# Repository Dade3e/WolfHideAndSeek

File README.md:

# WERERABBIT game
## Regole
### Wererabbit
Il gioco è metà tra nascondino e "ce l'hai":
Ogni giocatore ha un arma e i sensori ir,
Minimo di giocatori 3,
Il gioco si divide in wererabbit e rabbits.
Il wererabbit può sparare per passare il suo stato di wererabbit,
i rabbit non possono sparate, solo nascondersi o scappare.

A inizio gioco, il giocatore wererabbit conta per un tempo scelto dal gruppo, gli altri si nascondono.
Ogni giocatore rabbit, ogni circa 10 secondi invia un impulso a 866mhz, il quale è ricevuto dal wererabbit,
che lo visualizza sullo schermo come intensita di segnale trasformata circa in metri e lo aiuterà a cercare i rabbit.

Quando un wererabbit trova e colpisce un rabbit, il colpito diventerà in 60 sec il nuovo wererabbit e il vecchio wererabbit diventerà un rabbit.
Inoltre il vecchio wererabbit è immune al nuovo, ma solo a quello, non ai successivi.

Allo scadere del tempo mostrato a display, perde chi è il wererabbit o lo sta diventando.

### Infected
Ogni giocatore ha un arma e i ricevitori ir.
Il gioco si divide in infetto e sani.

Il gioco inizia con l'infetto che si nasconde.
L'infetto ha il sensore di prossimità il quale vede la distanza dai sani.
Se un sano entra nel raggio dei 5 metri da un infetto, l'infetto può premere il grilletto per infettare il sano.
Se un sano gli spara prima, l'infetto muore.

Il gioco finisce con lo scadere del tempo.
Vincono i più numerosi tra sani e infetti.

### Deathmatch
Classico deathmatch a scquadre o tutti contro tutti,
Se si imposta l'id team a 99, non ci sono squadre e sarà tutti contro tutti.
Una volta colpiti anche solo una volta si muore.
Il gioco finisce allo scadere del tempo.
TODO: vincita?
TODO: tornare alla base per riprendere vita?

### Materiali utilizzati:
- Presa Jack verticale 4 poli: https://www.amazon.it/dp/B089222S84?psc=1&ref=ppx_yo2ov_dt_b_product_details
- EDISION 05-00-0017 Cavo Jack a IR: https://www.amazon.it/dp/B08612KY32?psc=1&ref=ppx_yo2ov_dt_b_product_details
- Esp LoRa32: https://www.amazon.it/dp/B07RWYJQPT?psc=1&ref=ppx_yo2ov_dt_b_product_details
- Led IR SFH 4544: https://it.rs-online.com/web/p/led-a-infrarossi/8108247?sra=pstk
- Transistor 2N2222
- Resistenza da 510/470 Ohm
- Resistenza da 33/27 Ohm
- Pulsante 7 mm: https://www.amazon.it/Gebildet-Precablato-Momentaneo-Temporanei-Ferroviario/dp/B083K1YCZK/ref=sr_1_7?keywords=pulsante&qid=1673539022&sr=8-7&th=1
- Finecorsa da usare come grilletto, forse: https://www.amazon.it/InduSKY-Interruttore-Finecorsa-interruttore-Momentaneo/dp/B08736V215/ref=sr_1_21?keywords=finecorsa&qid=1673539142&sprefix=finecorsa%2Caps%2C115&sr=8-21 
- Morsettiera a vite 2.54: https://www.amazon.it/dp/B08VRD69B6?psc=1&smid=A1LEBA88GLK1VX&ref_=chk_typ_imgToDp

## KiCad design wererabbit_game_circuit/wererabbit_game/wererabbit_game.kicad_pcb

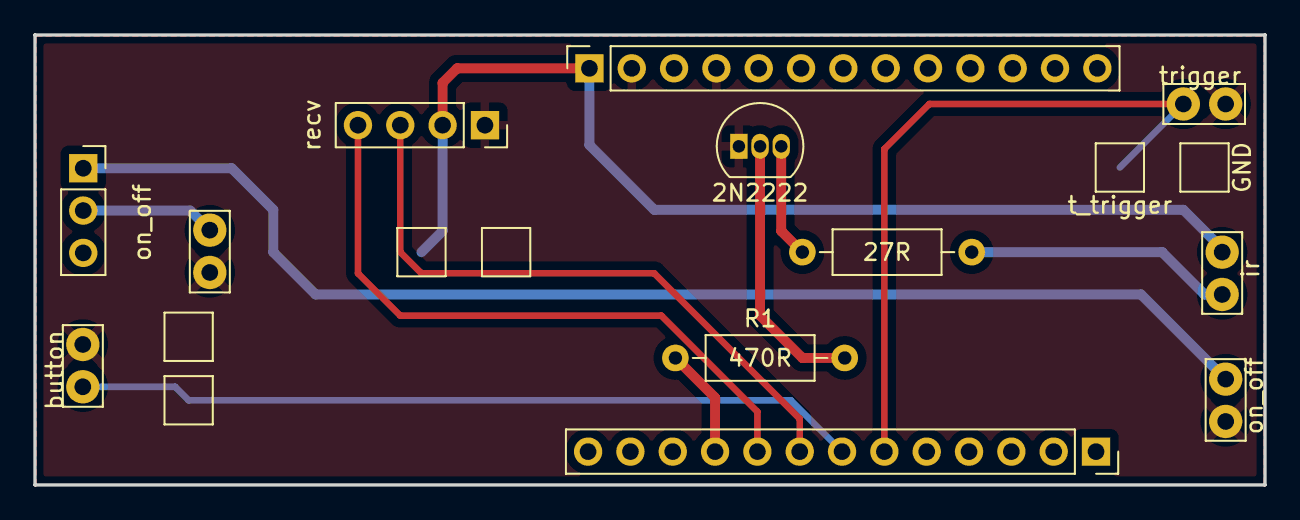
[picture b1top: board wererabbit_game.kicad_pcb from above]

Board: 2 copper layers, 73.8 x 27.0 mm, 18 parts (0 on the bottom side), 12 nets.

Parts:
J1, J2: Conn_01x13_Shielded; PinSocket_1x13_P2.54mm_Vertical
J6: ir; TestPoint_Bridge_Pitch2.54mm_Drill1.0mm
J7: trigger; TestPoint_Bridge_Pitch2.54mm_Drill1.0mm
J7a1: t_trigger; TestPoint_Pad_2.5x2.5mm
J8: button; TestPoint_Bridge_Pitch2.54mm_Drill1.0mm
J8a1: t_button; TestPoint_Pad_2.5x2.5mm
J9: recv; PinSocket_1x04_P2.54mm_Vertical
J10, J11: on_off; TestPoint_Bridge_Pitch2.54mm_Drill1.0mm
JGND1, JGND2, JGND3: GND; TestPoint_Pad_2.5x2.5mm
Jvcc1: VCC; TestPoint_Pad_2.5x2.5mm
Q1: 2N2222; TO-92_Inline
R1: 470R; R_Axial_DIN0207_L6.3mm_D2.5mm_P10.16mm_Horizontal
R2: 27R; R_Axial_DIN0207_L6.3mm_D2.5mm_P10.16mm_Horizontal
SW1: SW_DPDT_x2; PinSocket_1x03_P2.54mm_Vertical

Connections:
GND: J2.2, J2.4, J7.1, J8.1, J9.1, J10.1, J11.1, JGND1.1, JGND2.1, JGND3.1, Q1.1 (E)
unnamed: J1.6, J7.1, J7a1.1
unnamed: J1.7, J8.1, J8a1.1
unnamed: J1.8, J9.3
unnamed: J1.9, J9.4
unnamed: J1.10, R1.1
unnamed: J10.1, SW1.1 (A)
unnamed: J11.1, SW1.2 (B)
unnamed: Q1.2 (B), R1.2
unnamed: Q1.3 (C), R2.2
unnamed: J6.1, R2.1
VCC: J2.1, J6.1, J9.2, Jvcc1.1

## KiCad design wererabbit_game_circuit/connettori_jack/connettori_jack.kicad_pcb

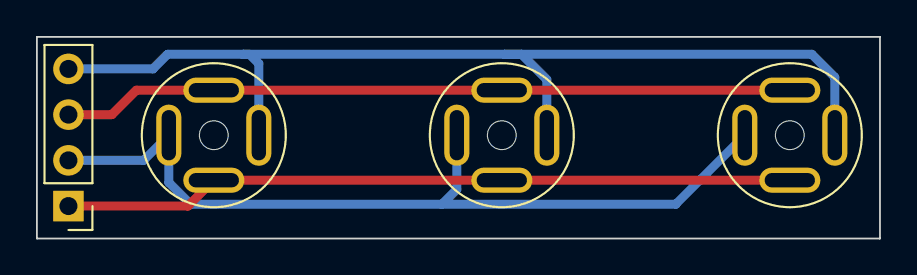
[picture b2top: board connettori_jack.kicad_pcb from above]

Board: 2 copper layers, 46.8 x 11.2 mm, 4 parts (0 on the bottom side), 4 nets.

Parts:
J1, J2, J3: AudioJack4; jack_4pins
J4: Conn_01x04; PinHeader_1x04_P2.54mm_Vertical

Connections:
unnamed: J1.3, J2.3, J3.3, J4.3
unnamed: J1.4, J2.4, J3.4, J4.4
unnamed: J1.1, J2.1, J3.1, J4.1
unnamed: J1.2, J2.2, J3.2, J4.2

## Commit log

2023-01-04 Add files
    Aggiunti tutti i file, il prototipo cosi funziona
2023-01-08 Aggiornato codice
2023-01-09 spostati files
2023-01-09 Aggiunte nuove immagini
2023-01-10 Aggiornato codice e aggiunte immagini
2023-01-10 corretto bug id e migliorata distanza
2023-01-10 migliorata grafica
2023-01-10 spreadingFactor, grafica e test
2023-01-11 aggiornamenti
2023-01-12 Pulizia progetto
2023-01-12 pulizia codice
2023-01-12 ttgo lora32 pinout
2023-01-12 Aggiunti schematici
2023-01-12 Readme con materiali usati
2023-01-12 Aggiunto timer e pulizia array
    Ho implementato il timer di gioco e trovato il modo di pulire ogni 30 sec e che i coniglietti siano circa sempre visibili, pulendo appena prima di reinserire un coniglietto.
2023-01-12 start up con grilletto
    il gioco inizia se si preme per 2 sec e rilascia il grilletto
2023-01-13 creato infected game
2023-01-15 aggiunto stato 2
    nel gioco infetti per mostrare la schermata che hai infettato ho aggiunto lo stato 2
2023-01-24 Aggiunto scritte alla pcb
2023-04-03 Nuove immagini
2023-04-03 Lora sender e finder
2023-04-04 Abbassato spreadingFactor a 9
2023-04-04 Migliorata gestione
2023-04-04 Vecchia versione ma funzionante
2023-04-04 Nuova versione infected rabbit
2023-04-04 Aggiornato finder e sender lora
2023-04-05 Corretta nome variabile
2023-04-05 Aggiunta modalita deathmatch
2023-04-05 Aggiornate regole
2023-04-05 Aggiunte parti per gestione vincitore
2023-04-06 Rinominato e migliorato controllo vincita
2023-04-06 Corretta grafica
2023-04-06 Aggiunta gestione led
2023-04-06 Aggiunto controllo vincita tutti contro tutti
2023-04-06 Migliorata gestione vincita
2023-04-06 Aggiornato README
2023-04-08 Corretto led e comunicazione lora
2023-04-09 migliorata giocabilita
